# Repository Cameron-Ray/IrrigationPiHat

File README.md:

# **Irrigation System μPiHAT <br>for RaspberryPi Zero**

The irrigation PiHAT can be used for the irrigation of small gardens/vegetable patches via soil moisture level sensing and water dispensing. It may also be used in lab environments where scientists need to hold the moisture level of the soil at a constant level.

An optional configuration, which shows the modular ability of the HAT, is to replace the moisture sensors with a float switch or humidity sensor to either fill up pools; ponds; or water tanks or to operate ventilation systems if an enclosed space reaches a maximum humidity level.

The PiHAT will allow more advanced users to continuously perform measurements or monitor the soil moisture levels by sending its input from the sensors into the main Pi GPIO header.
<br><br>

---

# Table of Contents

1. [**Getting Started**](#getting-started)

2. **How To Operate The...**

   - [Amplifier Module](How-Tos/DesignProcess.md#amplifier-module)
   - [LED Module](How-Tos/DesignProcess.md#led-module)
   - [Power Module](How-Tos/DesignProcess.md#power-module)

3. **Circuit Design Process**

   - [Requirements and Specifications](<Requirements & Specifications.pdf>)
   - [Simulation Output](<Simulation Files/SimulationPlots>)
   - [Final Individual Circuit Schematics](<Individual Module Schematics>)
   - [Combined Circuit Schematic](<Combined Schematic & PCB/Main Circuit.sch>)

4. **Final PCB Resources**

   - [KiCAD PCB Design File](<Combined Schematic & PCB/Main Circuit.kicad_pcb>)
   - [Bill of Materials](<Combined Schematic & PCB/BillOfMaterials.md>)
   - [Manufacturing Notes](How-Tos/ManufacturingNotes.md)

5. [**Contributing To This Repo**](CONTRIBUTING.md)

---

# Getting Started

Here's how to get started with your own Irrigation System PiHAT project!

## **Step 1:**

Clone this repository to your computer to get started by using the following command line git command:<br>
`git clone https://github.com/ryxcam002/IrrigationPiHat`<br><br>

## **Step 2:**

Change directory into the newly cloned repo using:<br>
`cd IrrigationPiHat`<br><br>

## **Step 3:**

Make sure you have the latest version of KiCAD and LTSpice installed. The download links to these open source programs can be found at:<br>
KiCAD - https://www.kicad.org/download/<br>
LTSpice - https://www.analog.com/en/design-center/design-tools-and-calculators/ltspice-simulator.html<br><br>

## **Step 4:**

Go through the design files to check if all is working well. If you wish to make any changes to the design, pay particular attention to the `Individual Module Schematics`, `Combined Schematic & PCB`, and `Simulation Files` folders.<br><br>

- The `Individual Module Schematics` folder is where you will find each submodule KiCAD schematic design. These can be modified individually to suit your needs.<br>
- The `Simulation Files` folder is where the V2.0 circuits weere simulated to determine if all parameters ffor circuit components were setup correctly.<br>
- The `Combined Schematic & PCB` folder is where all the submodules have been combined to form a single schematic, ready for PCB footprint assignment and BOM generation.<br><br>

## **Step 5:**

Generate gerber files for final PCB manufacturing. To do this, open the `.kicad_pcb` file in the `Combined Schematic & PCB` folder, ensure that all components/PCB specifications are correct and generate the gerber files from there.

## **Step 6:**

Manufacture PCB and solder all components or have this done by the manufacturer if they support this. You now have a micro irrrigation controller!

---

# Contributing To This Repo

See the full contribution documentation [here](CONTRIBUTING.md).

---

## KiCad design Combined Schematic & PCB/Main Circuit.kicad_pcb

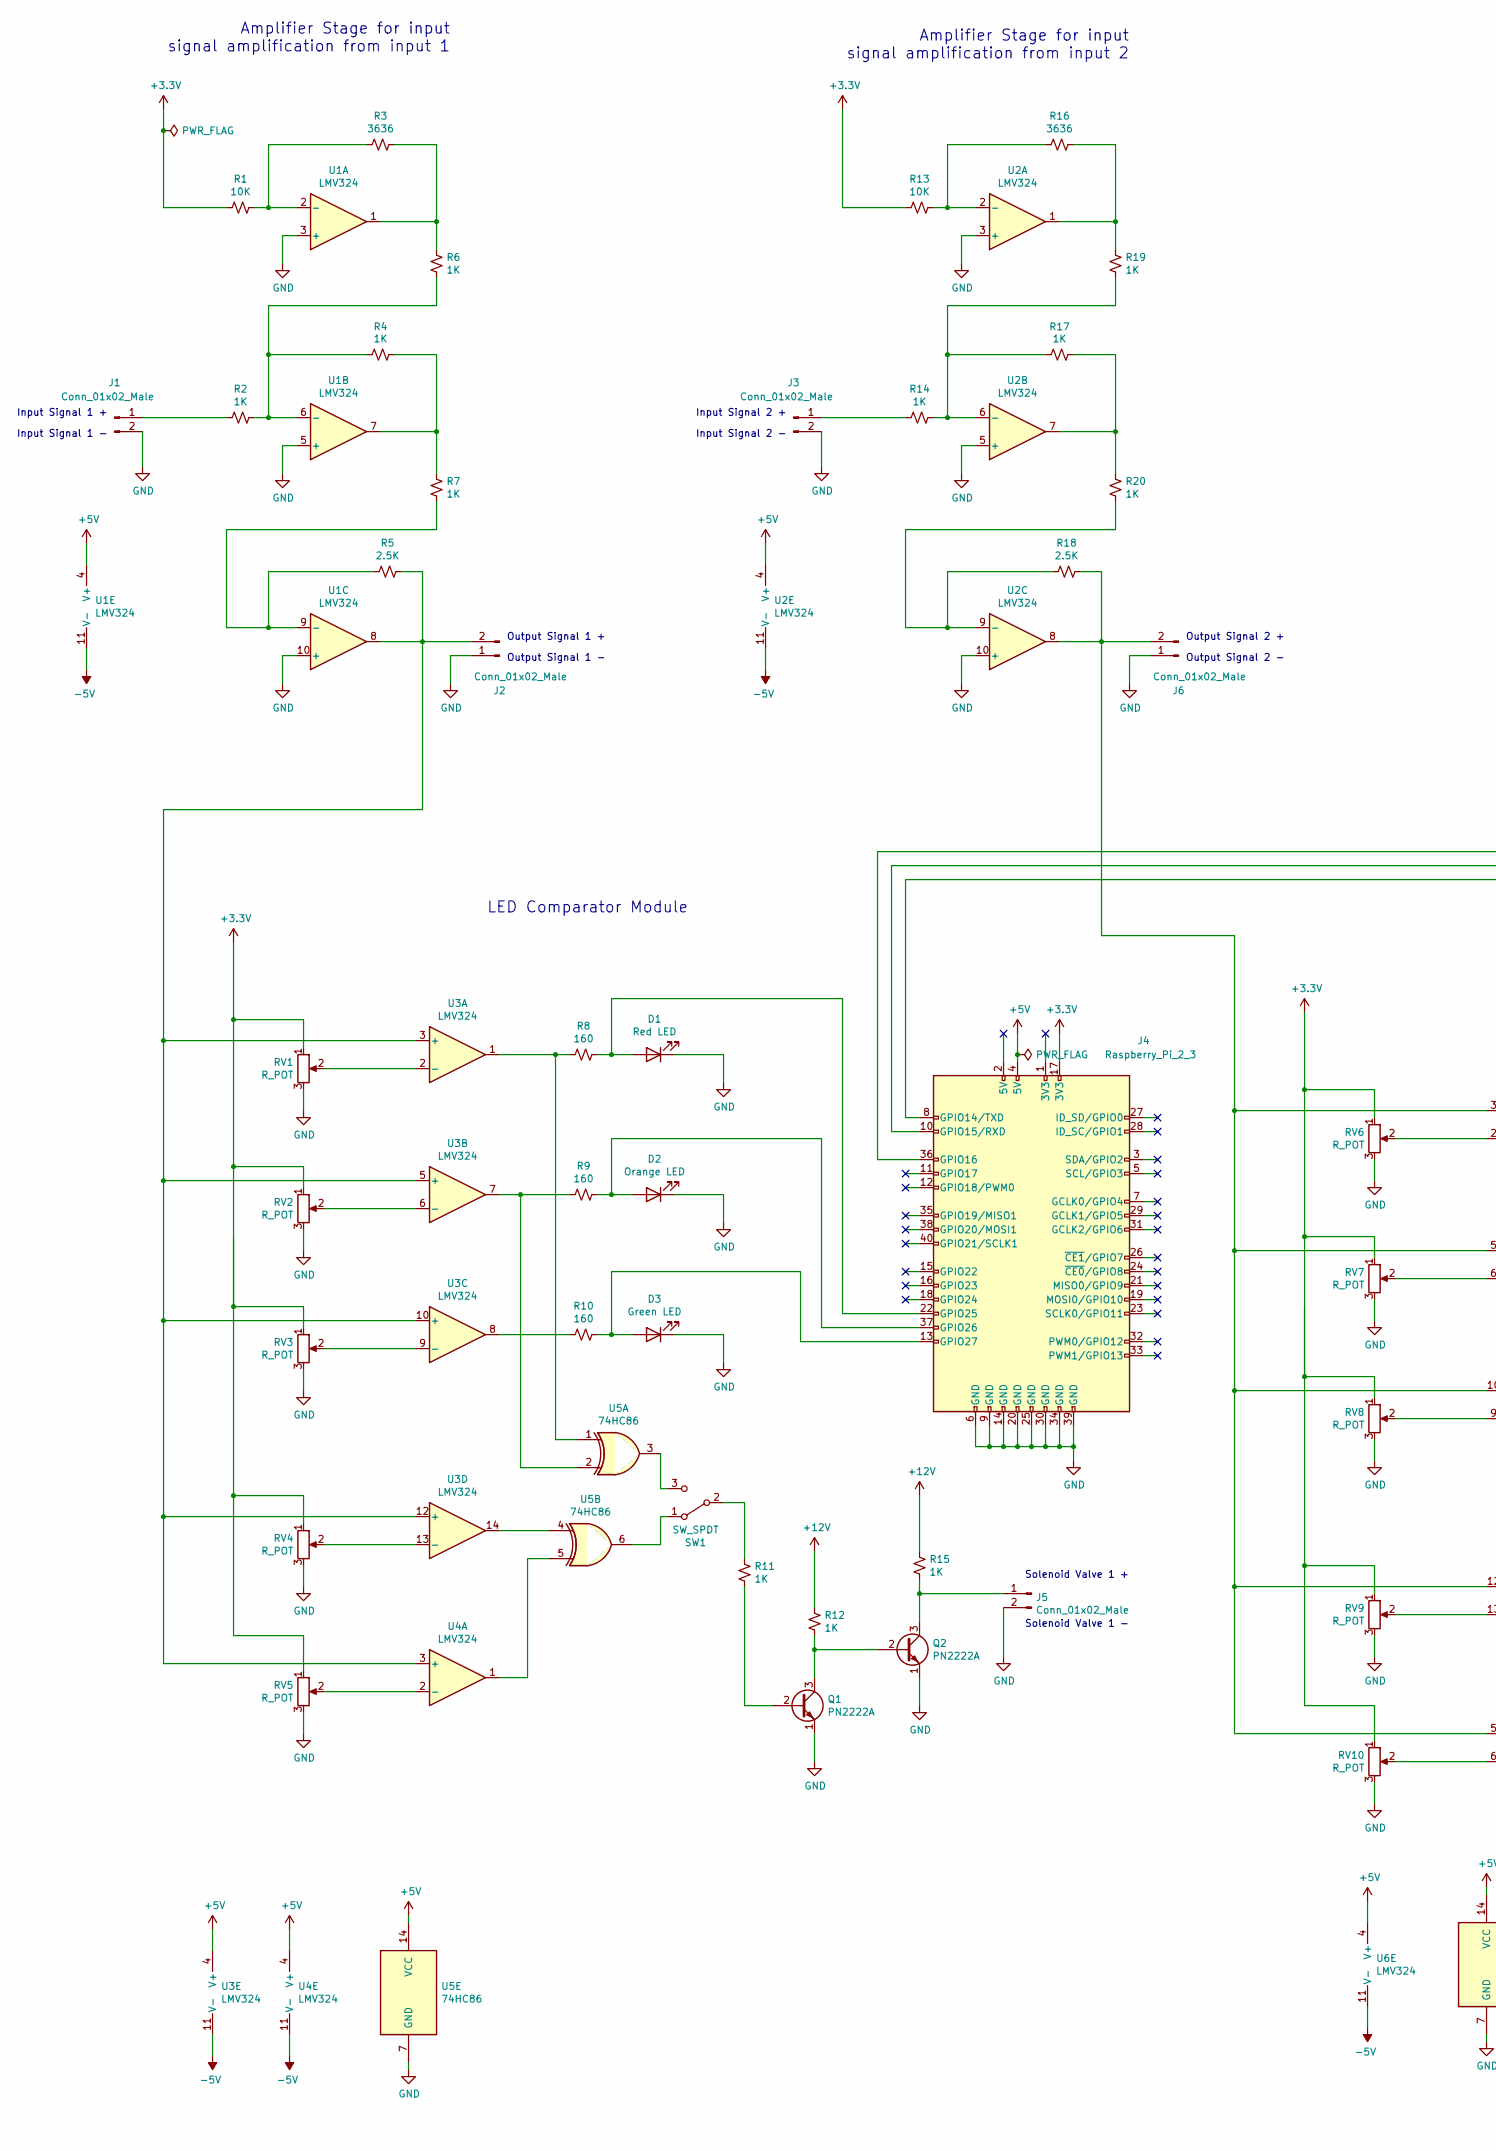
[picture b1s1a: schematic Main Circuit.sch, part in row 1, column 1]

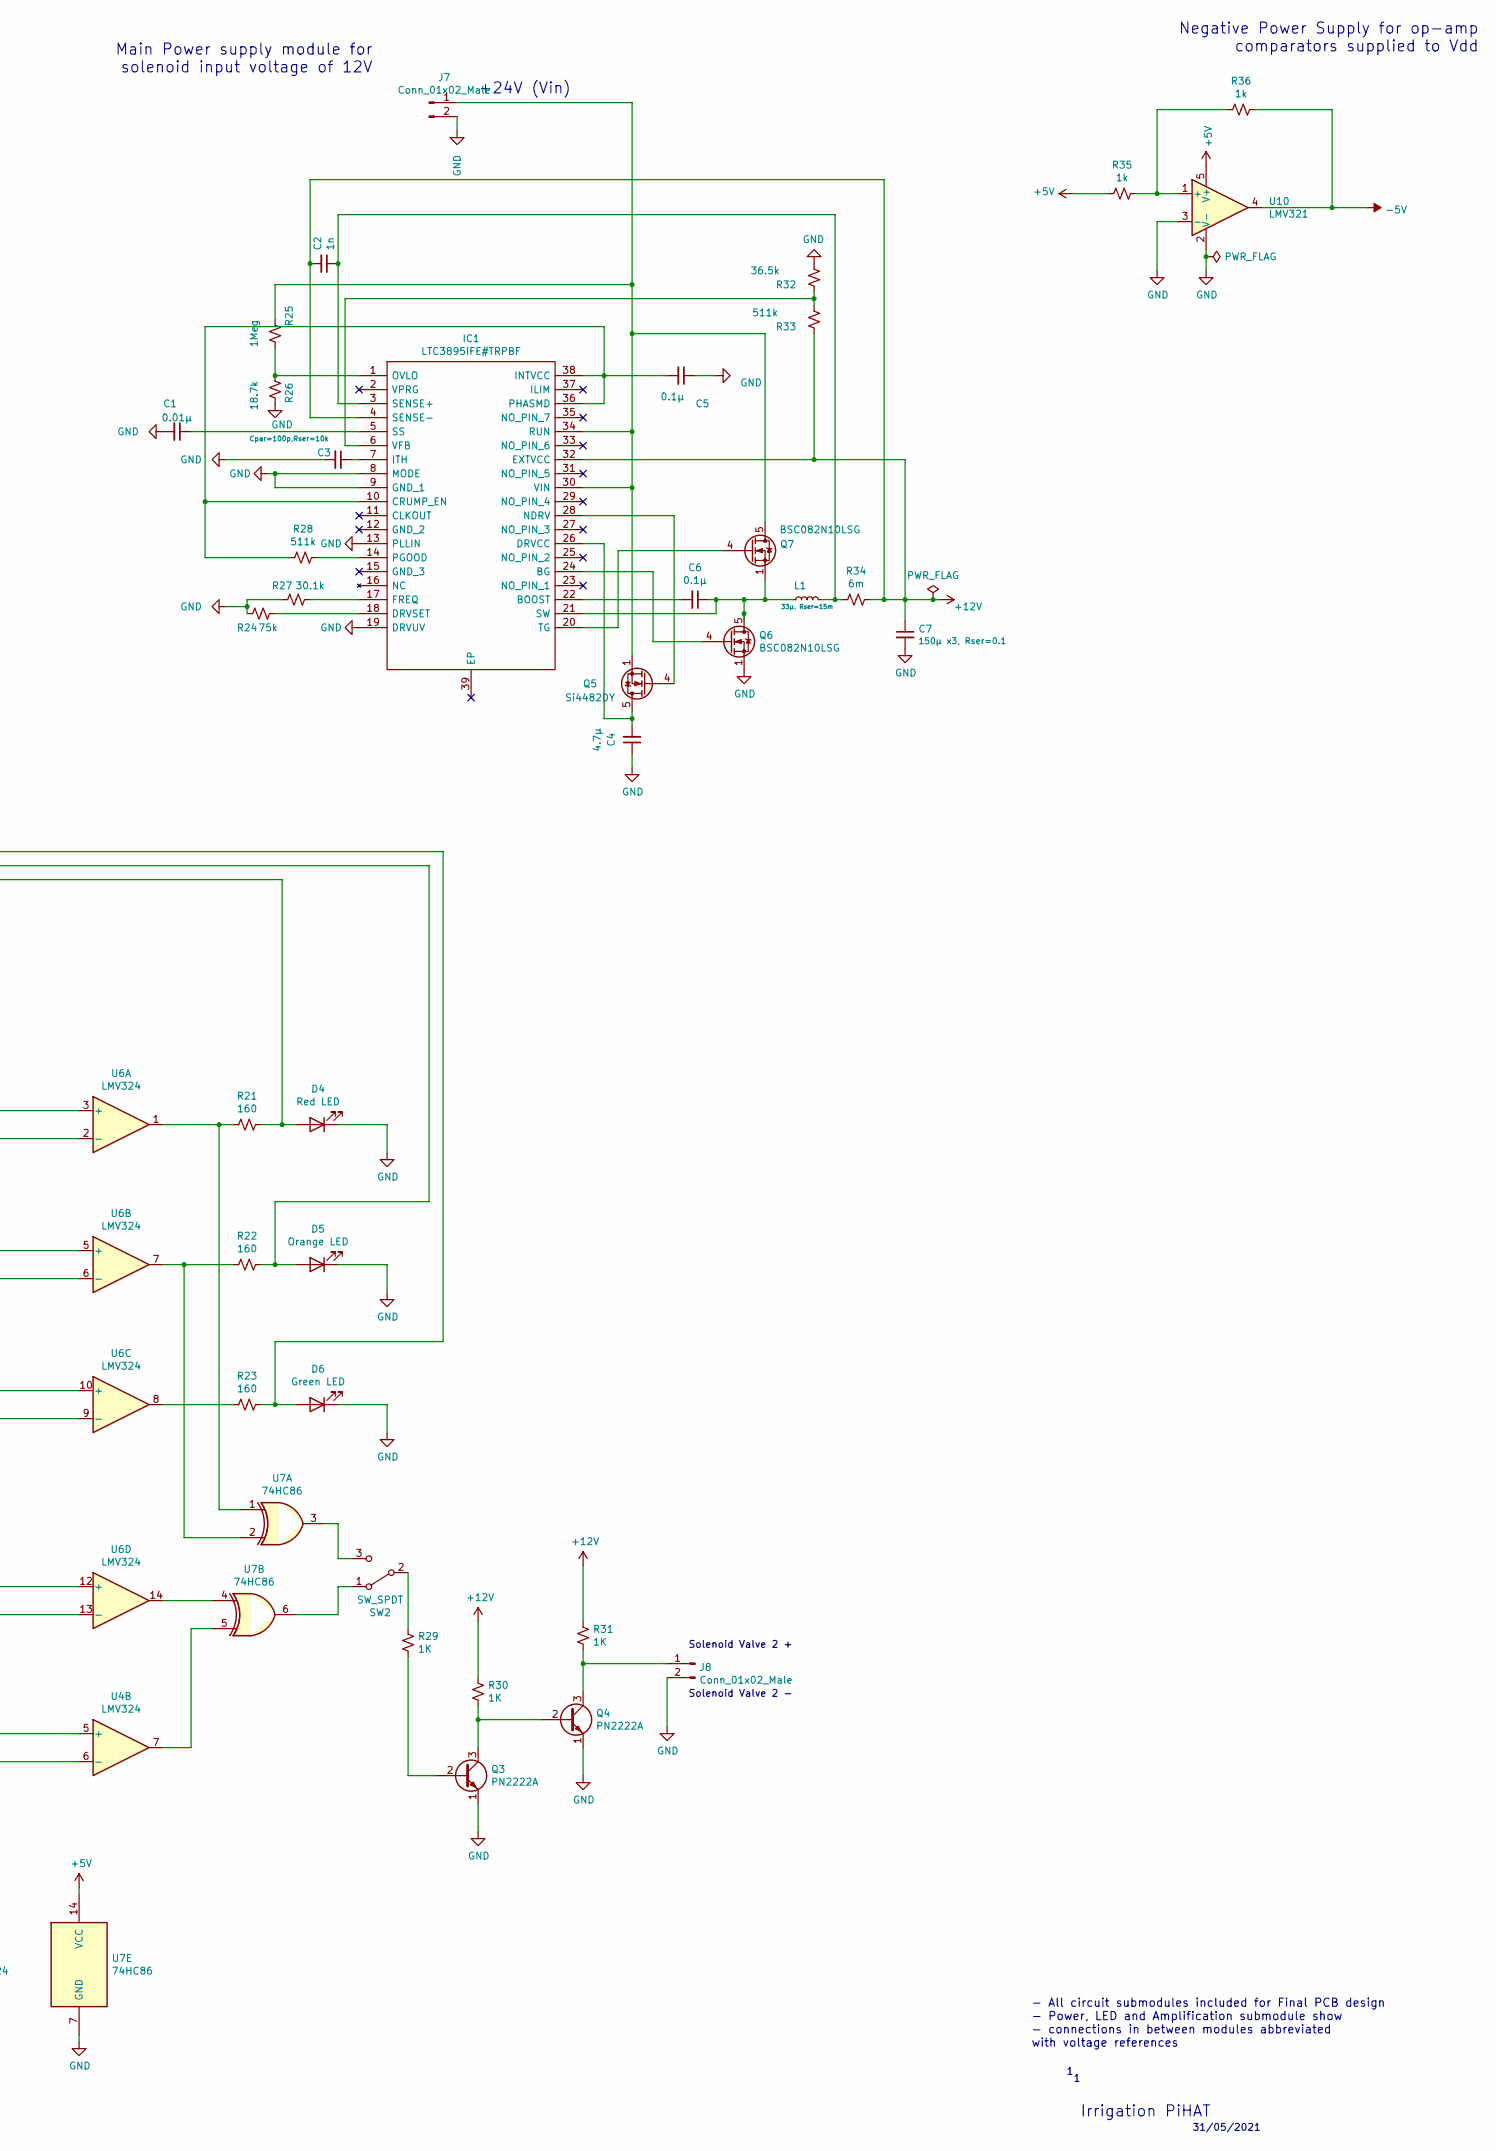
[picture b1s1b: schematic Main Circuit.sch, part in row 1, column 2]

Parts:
C1: 0.01µ; C_0201_0603Metric
C2: 1n; C_0201_0603Metric
C3: Cpar=100p,Rser=10k; C_0201_0603Metric
C4: 4.7µ; C_0201_0603Metric
C5, C6: 0.1µ; C_0201_0603Metric
C7: 150µ x3, Rser=0.1; C_0201_0603Metric
D1, D4: Red LED; LED_0201_0603Metric
D2, D5: Orange LED; LED_0201_0603Metric
D3, D6: Green LED; LED_0201_0603Metric
IC1: LTC3895IFE#TRPBF; SOP50P640X120-39N; Manufacturer_Part_Number LTC3895IFE#TRPBF; Mouser Part Number 584-LTC3895IFE#TRPBF
J1, J2, J3, J5, J6, J7, J8: Conn_01x02_Male; PinHeader_1x02_P1.00mm_Vertical
J4: Raspberry_Pi_2_3; Raspberry_Pi_Zero_Socketed_THT_FaceDown_MountingHoles
L1: 33µ, Rser=15m; L_1206_3216Metric
Q1, Q2, Q3, Q4: PN2222A; SOT-323_SC-70
Q5: Si4482DY; TDSON-8-1
Q6, Q7: BSC082N10LSG; TDSON-8-1
R1, R13: 10K; R_0201_0603Metric
R2, R4, R6, R7, R11, R12, R14, R15, R17, R19, R20, R29, R30, R31: 1K; R_0201_0603Metric
R3, R16: 3636; R_0201_0603Metric
R5, R18: 2.5K; R_0201_0603Metric
R8, R9, R10, R21, R22, R23: 160; R_0201_0603Metric
R24: 75k; R_0201_0603Metric
R25: 1Meg; R_0201_0603Metric
R26: 18.7k; R_0201_0603Metric
R27: 30.1k; R_0201_0603Metric
R28, R33: 511k; R_0201_0603Metric
R32: 36.5k; R_0201_0603Metric
R34: 6m; R_0201_0603Metric
R35, R36: 1k; R_0201_0603Metric
RV1, RV2, RV3, RV4, RV5, RV6, RV7, RV8, RV9, RV10: R_POT; Potentiometer_Bourns_3314G_Vertical
SW1, SW2: SW_SPDT; JS102011JCQN
U1, U2, U3, U4, U6: LMV324; SOIC-14_3.9x8.7mm_P1.27mm
U5, U7: 74HC86; SOIC-14_3.9x8.7mm_P1.27mm
U10: LMV321; TSOT-23-5

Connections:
+3V3: J4.17 (3V3), R1.2, R13.2, RV1.1, RV2.1, RV3.1, RV4.1, RV5.1, RV6.1, RV7.1, RV8.1, RV9.1, RV10.1
+5V: J4.4 (5V), R35.2, U1.4 (V+), U2.4 (V+), U3.4 (V+), U4.4 (V+), U5.14 (VCC), U6.4 (V+), U7.14 (VCC), U10.5 (V+)
+12V: C2.2, C7.1, IC1.4 (SENSE-), IC1.32 (EXTVCC), R12.1, R15.1, R30.1, R31.1, R33.1, R34.1
-5V: R36.1, U1.11 (V-), U2.11 (V-), U3.11 (V-), U4.11 (V-), U6.11 (V-), U10.4
GND: C1.2, C3.2, C4.1, C5.1, C7.2, D1.1 (K), D2.1 (K), D3.1 (K), D4.1 (K), D5.1 (K), D6.1 (K), IC1.8 (MODE), IC1.9 (GND_1), IC1.13 (PLLIN), IC1.19 (DRVUV), J1.2, J2.1, J3.2, J4.6 (GND), J4.9 (GND), J4.14 (GND), J4.20 (GND), J4.25 (GND), J4.30 (GND), J4.34 (GND), J4.39 (GND), J5.2, J6.1, J7.2, J8.2, Q1.1 (E), Q2.1 (E), Q3.1 (E), Q4.1 (E), Q6.1 (S), Q6.2 (S), Q6.3 (S), R24.2, R26.2, R27.2, R32.2, RV1.3, RV2.3, RV3.3, RV4.3, RV5.3, RV6.3, RV7.3, RV8.3, RV9.3, RV10.3, U1.3 (+), U1.5 (+), U1.10 (+), U2.3 (+), U2.5 (+), U2.10 (+), U5.7 (GND), U7.7 (GND), U10.2 (V-), U10.3 (-)
unnamed: C1.1, IC1.5 (SS)
unnamed: C2.1, IC1.3 (SENSE+), L1.2, R34.2
unnamed: C3.1, IC1.7 (ITH)
unnamed: C4.2, IC1.26 (DRVCC), Q5.5 (D)
unnamed: C5.2, IC1.10 (CRUMP_EN), IC1.36 (PHASMD), IC1.38 (INTVCC), R28.2
unnamed: C6.1, IC1.21 (SW), L1.1, Q6.5 (D), Q7.1 (S), Q7.2 (S), Q7.3 (S)
unnamed: C6.2, IC1.22 (BOOST)
unnamed: D1.2 (A), J4.22 (GPIO25), R8.1
unnamed: D2.2 (A), J4.37 (GPIO26), R9.1
unnamed: D3.2 (A), J4.13 (GPIO27), R10.1
unnamed: D4.2 (A), J4.8 (GPIO14/TXD), R21.1
unnamed: D5.2 (A), J4.10 (GPIO15/RXD), R22.1
unnamed: D6.2 (A), J4.36 (GPIO16), R23.1
unnamed: IC1.1 (OVLO), R25.2, R26.1
unnamed: IC1.6 (VFB), R32.1, R33.2
unnamed: IC1.14 (PGOOD), R28.1
unnamed: IC1.17 (FREQ), R27.1
unnamed: IC1.18 (DRVSET), R24.1
unnamed: IC1.20 (TG), Q7.4 (G)
unnamed: IC1.24 (BG), Q6.4 (G)
unnamed: IC1.28 (NDRV), Q5.4 (G)
unnamed: IC1.30 (VIN), IC1.34 (RUN), J7.1, Q5.1 (S), Q5.2 (S), Q5.3 (S), Q7.5 (D), R25.1
unnamed: J1.1, R2.2
unnamed: J2.2, R5.1, U1.8, U3.3 (+), U3.5 (+), U3.10 (+), U3.12 (+), U4.3 (+)
unnamed: J3.1, R14.2
unnamed: J5.1, Q2.3 (C), R15.2
unnamed: J6.2, R18.1, U2.8, U4.5 (+), U6.3 (+), U6.5 (+), U6.10 (+), U6.12 (+)
unnamed: J8.1, Q4.3 (C), R31.2
unnamed: Q1.2 (B), R11.2
unnamed: Q1.3 (C), Q2.2 (B), R12.2
unnamed: Q3.2 (B), R29.2
unnamed: Q3.3 (C), Q4.2 (B), R30.2
unnamed: R1.1, R3.2, U1.2 (-)
unnamed: R2.1, R4.2, R6.2, U1.6 (-)
unnamed: R3.1, R6.1, U1.1
unnamed: R4.1, R7.1, U1.7
unnamed: R5.2, R7.2, U1.9 (-)
unnamed: R8.2, U3.1, U5.1
unnamed: R9.2, U3.7, U5.2
unnamed: R10.2, U3.8
unnamed: R11.1, SW1.2 (B)
unnamed: R13.1, R16.2, U2.2 (-)
unnamed: R14.1, R17.2, R19.2, U2.6 (-)
unnamed: R16.1, R19.1, U2.1
unnamed: R17.1, R20.1, U2.7
unnamed: R18.2, R20.2, U2.9 (-)
unnamed: R21.2, U6.1, U7.1
unnamed: R22.2, U6.7, U7.2
unnamed: R23.2, U6.8
unnamed: R29.1, SW2.2 (B)
unnamed: R35.1, R36.2, U10.1 (+)
unnamed: RV1.2, U3.2 (-)
unnamed: RV2.2, U3.6 (-)
unnamed: RV3.2, U3.9 (-)
unnamed: RV4.2, U3.13 (-)
unnamed: RV5.2, U4.2 (-)
unnamed: RV6.2, U6.2 (-)
unnamed: RV7.2, U6.6 (-)
unnamed: RV8.2, U6.9 (-)
unnamed: RV9.2, U6.13 (-)
unnamed: RV10.2, U4.6 (-)
unnamed: SW1.1 (A), U5.6
unnamed: SW1.3 (C), U5.3
unnamed: SW2.1 (A), U7.6
unnamed: SW2.3 (C), U7.3
unnamed: U3.14, U5.4
unnamed: U4.1, U5.5
unnamed: U4.7, U7.5
unnamed: U6.14, U7.4

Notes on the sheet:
Input Signal 1 +
Input Signal 1 -
Output Signal 1 +
Output Signal 1 -
Input Signal 2 +
Input Signal 2 -
Output Signal 2 +
Output Signal 2 -
Solenoid Valve 1 +
Solenoid Valve 1 -
Solenoid Valve 2 +
Solenoid Valve 2 -
+24V (Vin)
- All circuit submodules included for Final PCB design - Power, LED and Amplification submodule show - connections in between modules abbreviated with voltage references
Negative Power Supply for op-amp comparators supplied to Vdd
Main Power supply module for solenoid input voltage of 12V
Irrigation PiHAT
31/05/2021
Amplifier Stage for input signal amplification from input 2
Amplifier Stage for input signal amplification from input 1
LED Comparator Module

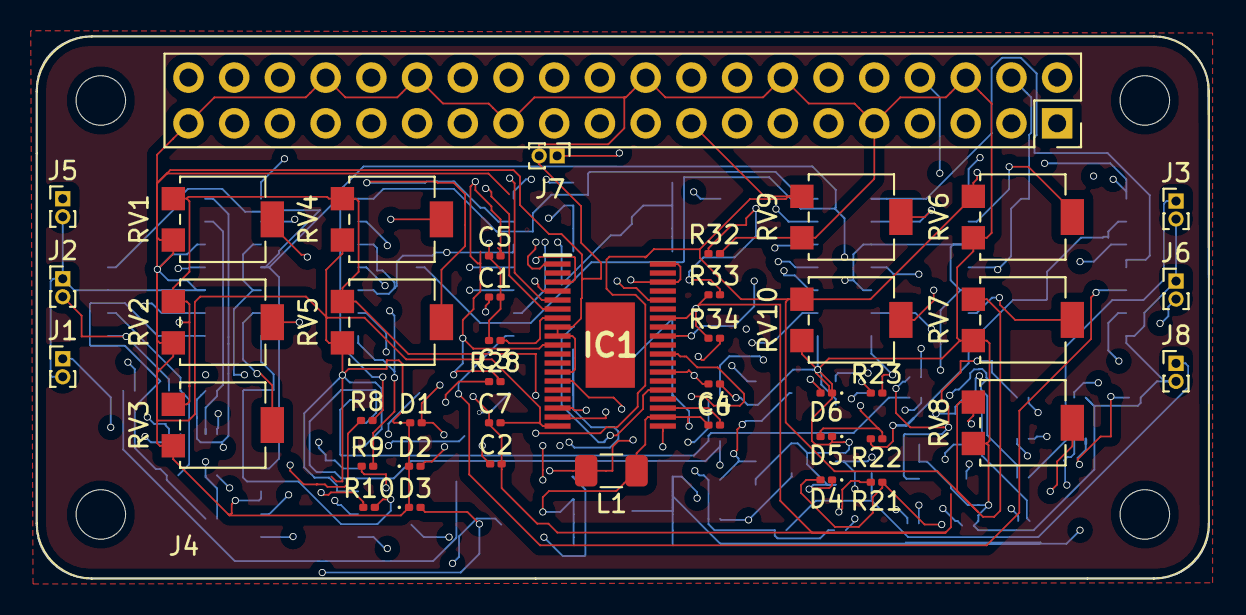
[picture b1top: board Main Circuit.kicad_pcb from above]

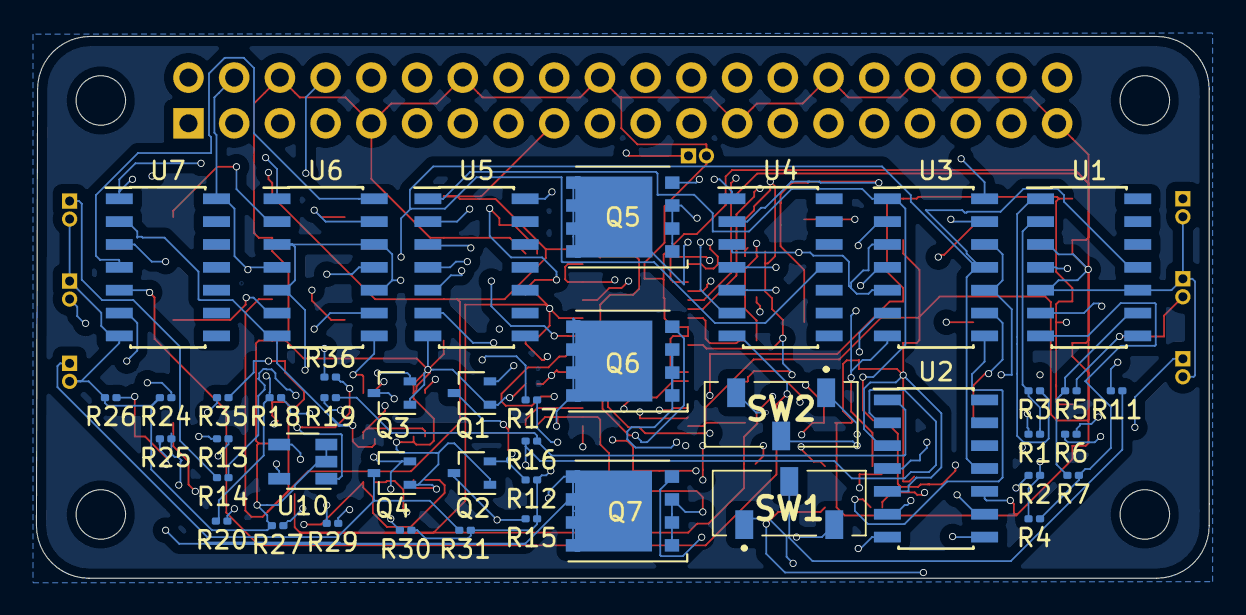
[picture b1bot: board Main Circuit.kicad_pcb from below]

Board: 6 copper layers, 65.2 x 30.1 mm, 86 parts (43 on the bottom side), 74 nets.

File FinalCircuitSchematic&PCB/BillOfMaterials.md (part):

# Bill of Materials

The table below shows the complete Bill of Materials for the project. These components may differ in value, depending on your application of the project. Datasheets are provided for only some of the components as this table was generated by the KiCAD electronic design tool and the tool has only a select offline database of component properties. To use the parts below which do not have a specified datasheet, make sure that you research a suitable component that matches the ratings of the listed component within some reasonable margin.

---

<br>

| Ref                                                              | Qnty | Value              | Part                            | Datasheet                                                                                                  | Description                                                                                            |
| ---------------------------------------------------------------- | ---- | ------------------ | ------------------------------- | ---------------------------------------------------------------------------------------------------------- | ------------------------------------------------------------------------------------------------------ |
| C1                                                               | 1    | 0.01µ              | Device:C_Small                  | ~                                                                                                          | Unpolarized capacitor, small symbol                                                                    |
| C2                                                               | 1    | 1n                 | Device:C_Small                  | ~                                                                                                          | Unpolarized capacitor, small symbol                                                                    |
| C3                                                               | 1    | Cpar=100p,Rser=10k | Device:C_Small                  | ~                                                                                                          | Unpolarized capacitor, small symbol                                                                    |
| C4                                                               | 1    | 4.7µ               | Device:C_Small                  | ~                                                                                                          | Unpolarized capacitor, small symbol                                                                    |
| C5, C6                                                           | 2    | 0.1µ               | Device:C_Small                  | ~                                                                                                          | Unpolarized capacitor, small symbol                                                                    |
| C7                                                               | 1    | 150µ x3, Rser=0.1  | Device:C_Small                  | ~                                                                                                          | Unpolarized capacitor, small symbol                                                                    |
| D1, D4                                                           | 2    | Red LED            | Device:LED                      | ~                                                                                                          | Light emitting diode                                                                                   |
| D2, D5                                                           | 2    | Orange LED         | Device:LED                      | ~                                                                                                          | Light emitting diode                                                                                   |
| D3, D6                                                           | 2    | Green LED          | Device:LED                      | ~                                                                                                          | Light emitting diode                                                                                   |
| IC1                                                              | 1    | LTC3895IFE#TRPBF   | LTC3895PartLib:LTC3895IFE#TRPBF | https://www.analog.com/media/en/technical-documentation/data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                             |                                                                                                        |
| J1, J2, J3, J5, J6, J7, J8                                       | 7    | Conn_01x02_Male    | Connector:Conn_01x02_Male       | ~                                                                                                          | Generic connector, single row, 01x02, script generated (kicad-library-utils/schlib/autogen/connector/) |
| J4                                                               | 1    | Raspberry_Pi_2_3   | Connector:Raspberry_Pi_2_3      | https://www.raspberrypi.org/documentation/hardware/raspberry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   | expansion header for Raspberry Pi 2 & 3                                                                |
| L1                                                               | 1    | 33µ, Rser=15m      | Device:L_Small                  | ~                                                                                                          | Inductor, small symbol                                                                                 |
| Q1, Q2, Q3, Q4                                                   | 4    | PN2222A            | Transistor_BJT:PN2222A          | http://www.fairchildsemi.com/ds/PN/PN2222A.pdf                                                             | 1A Ic, 40V Vce, NPN Transistor, General Purpose Transistor, TO-92                                      |
| Q5                                                               | 1    | Si4482DY           | Transistor_FET:BSC082N10LSG     | http://www.infineon.com/dgdl/Infineon-BSC082N10LS-DS-v01_07-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 | 100A Id, 100V Vds, OptiMOS N-Channel Power MOSFET, 8.2mOhm Ron, Qg (typ) 78.0nC, PG-TDSON-8            |
| Q6, Q7                                                           | 2    | BSC082N10LSG       | Transistor_FET:BSC082N10LSG     | http://www.infineon.com/dgdl/Infineon-BSC082N10LS-DS-v01_07-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 | 100A Id, 100V Vds, OptiMOS N-Channel Power MOSFET, 8.2mOhm Ron, Qg (typ) 78.0nC, PG-TDSON-8            |
| R1, R13                                                          | 2    | 10K                | Device:R_Small_US               | ~                                                                                                          | Resistor, small US symbol                                                                              |
| R2, R4, R6, R7, R11, R12, R14, R15, R17, R19, R20, R29, R30, R31 | 14   | 1K                 | Device:R_Small_US               | ~                                                                                                          | Resistor, small US symbol                                                                              |
| R3, R16                                                          | 2    | 3636               | Device:R_Small_US               | ~                                                                                                          | Resistor, small US symbol                                                                              |
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
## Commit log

2021-05-07 Sharepoint sync with git repo, no other changes made to resources
2021-05-08 Changed folder nam
2021-05-08 Updated directory naming conventions. Added Q1 simulation plots to the report doc. Copied LED & Amplifier subsystem circuit design files across to V1.0 as they are final from V0.1
2021-05-08 Add github URLs to final report doc for assignment marker to access simulation files easily
2021-05-21 Assignment 2 final submission and Power Submodule simulation files added
2021-05-28 V2 Power submodule corrected with actual IC from manufacturer's site. Added inverting -5V power supply for op-amp comparator Vdd rail. Created V2 folders and prepped final PCB folder for file creation
2021-05-28 Updated README with project description
2021-05-28 added README res folder
2021-06-03 Updated File structure and implemented gitignore fully for unecessary generated files. Final Schematic and PCB files added.
2021-06-03 Removing files that do not need to be tracked for final repo
2021-06-03 Updated gitignore
2021-06-03 Create LICENSE
2021-06-04 Updated Assignment 3 pdf with details about schematics. Cleaned up schematic files
2021-06-09 Contributing file added using open-source version. BOM added for overall circuit. Circuit simulation images added for final report as they need to be linked in reference docs (report).
2021-06-09 File structure cleaned again. Created final individual module schematic PDFs
2021-06-09 Added new md docs and created reqs and specs from old reporting. Needs to be updated
2021-06-09 Updated README and design process file
2021-06-09 Updated look of README. Content still to be added.
2021-06-09 Updated final schematic as incorrect switch packages were selected. Added external switch library
2021-06-09 Final changes made to Reqs and Specs doc
2021-06-13 Updated getting started content
2021-06-13 Complete Assignment 4 and PCB 3d images added
2021-06-13 Updated Power module How To
2021-06-13 Updated broken image links
2021-06-13 Updated Power Module How To with better formatting
2021-06-18 Updated File structure for more ease of use to end users. Major structure updates made for fresh feel and minimal assigment submission clutter
2021-06-18 How-To Documentation updated with corrected links as restructuring cause certain image and other hyperlinks to break
2021-06-18 Final Reference Manual added
